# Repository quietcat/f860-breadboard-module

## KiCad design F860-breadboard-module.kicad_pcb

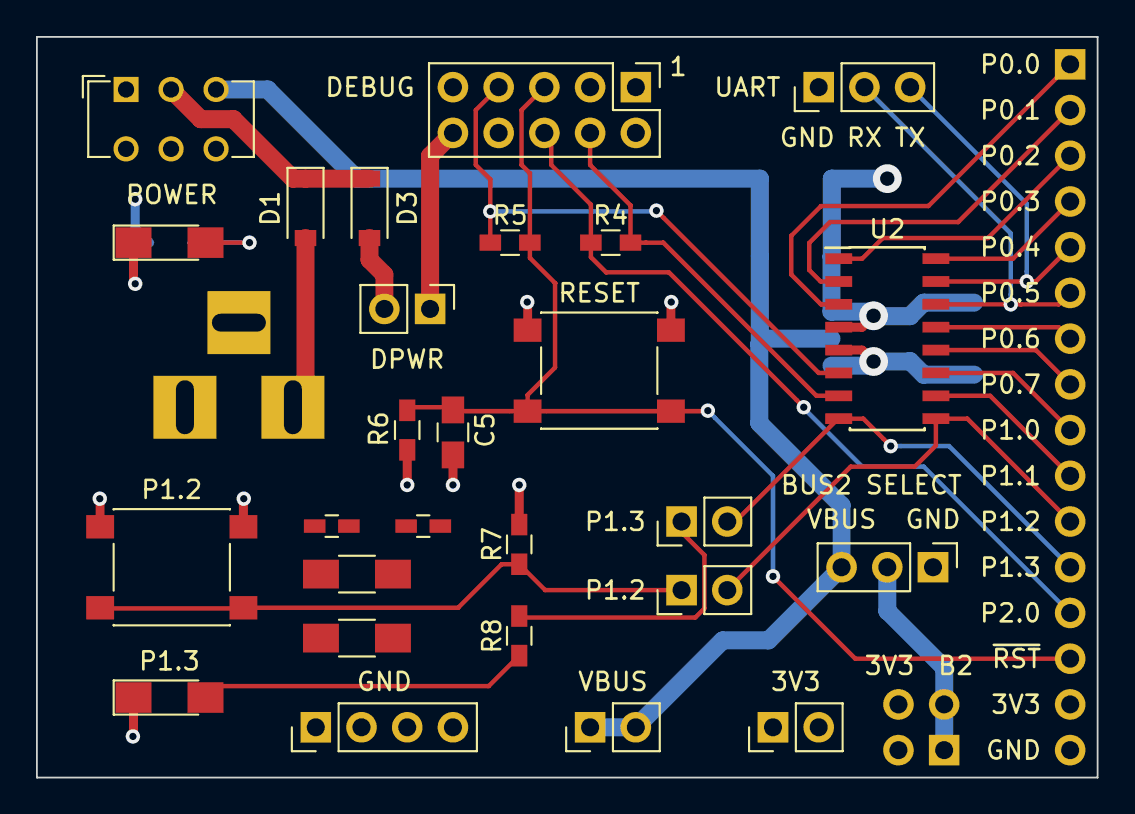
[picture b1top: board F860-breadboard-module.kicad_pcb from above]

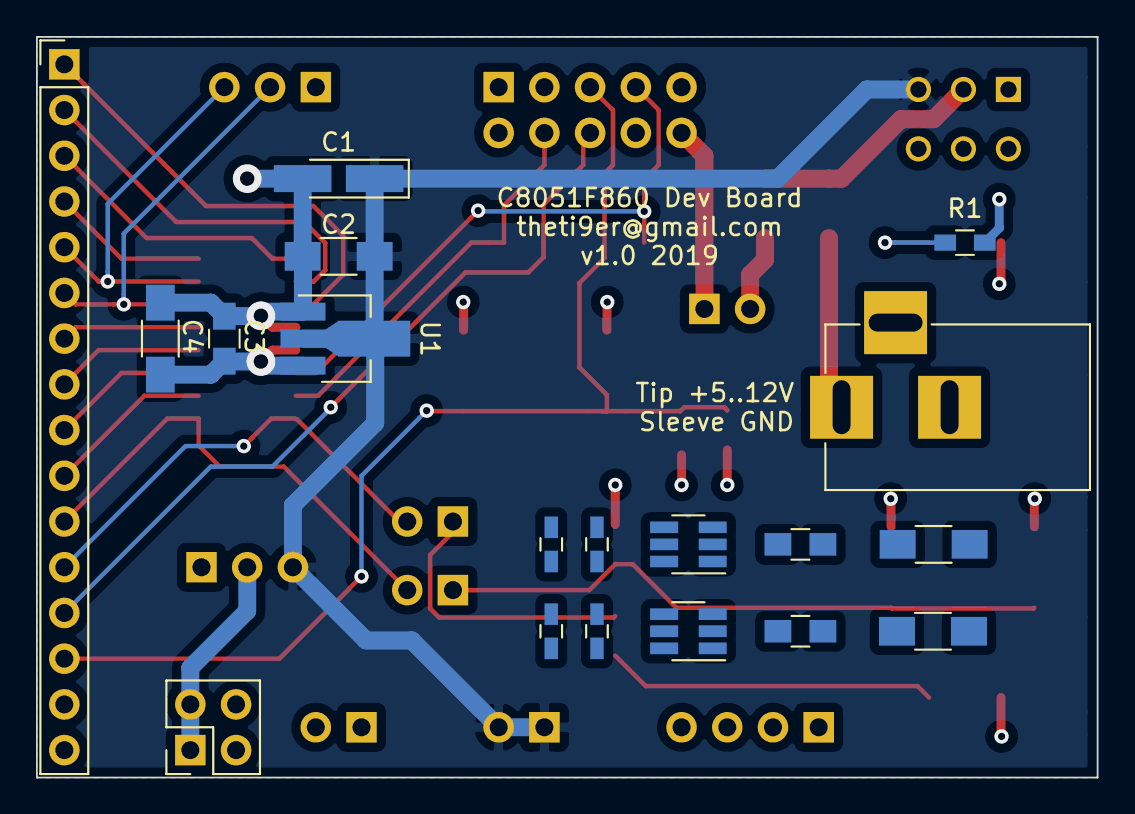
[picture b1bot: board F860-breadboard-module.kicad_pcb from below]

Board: 4 copper layers, 58.9 x 41.1 mm, 32 parts (9 on the bottom side), 28 nets.

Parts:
C1: 22.0; CP_Tantalum_Case-A_EIA-3216-18_Hand
C2, C4: 1.0; C_1206_HandSoldering
C3, C5: 0.1; C_0805_HandSoldering
D1, D3: STPS140Z; D_SOD-123
D2: PWR; LED_1206_HandSoldering
D4: P1.3; LED_1206_HandSoldering
J1: 5-12V; BARREL_JACK
J2: BOARD; Socket_Strip_Straight_1x16_Pitch2.54mm
J3: BUS2 SELECT; Pin_Header_Straight_1x03_Pitch2.54mm
J4: BUS1-2; Pin_Header_Straight_2x02_Pitch2.54mm
J6: VBUS; Pin_Header_Straight_1x02_Pitch2.54mm
J7: 3V3; Pin_Header_Straight_1x02_Pitch2.54mm
J8: GND; Pin_Header_Straight_1x04_Pitch2.54mm
J9: UART; Pin_Header_Straight_1x03_Pitch2.54mm
J10: DEBUG; Pin_Header_Straight_2x05_Pitch2.54mm
JP1: DPWR; Pin_Header_Straight_1x02_Pitch2.54mm
JP2: P1.2; Pin_Header_Straight_1x02_Pitch2.54mm
JP3: P1.3; Pin_Header_Straight_1x02_Pitch2.54mm
R1, R8: 470; R_0603_HandSoldering
R4, R5, R6: 1K0; R_0603_HandSoldering
R7: 3K3; R_0603_HandSoldering
SW1: POWER; SW_CuK_JS202011CQN_DPDT_Straight
SW2: RESET; SW_SPST_PTS645
SW3: P1.2; SW_SPST_PTS645
U1: MCP1700-3302E_SOT89; SOT-89-3_Handsoldering
U2: C8051F860-C-GS; SOIC-16_3.9x9.9mm_Pitch1.27mm

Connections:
+3V3: C3.1, C4.1, J2.15, J4.3, J4.4, J7.1, J7.2, R1.1, R6.2, R7.1, U1.3, U2.5
/C2CK: J10.7, R5.1, U2.6
/C2D: J10.4, R4.1, U2.7
/P0_0: J2.1, U2.3
/P0_1: J2.2, U2.2
/P0_2: J2.3, U2.1
/P0_3: J2.4, U2.16
/P0_4: J2.5, J9.3, U2.15
/P0_5: J2.6, J9.2, U2.14
/P0_6: J2.7, U2.13
/P0_7: J2.8, U2.12
/P1_0: J2.9, U2.11
/P1_1: J2.10, U2.10
/P1_2: J2.11, JP2.2, U2.9
/P1_3: J2.12, JP3.2, U2.8
/P2_0: J2.13, J10.6, R4.2
/VBUS0: D1.1, D3.1, SW1.2
/~RST: C5.1, J2.14, J10.5, R5.2, R6.1, SW2.2
GND: C1.2, C2.2, C3.2, C4.2, C5.2, D2.1, D4.1, J1.2, J2.16, J3.1, J8.1, J8.2, J8.3, J8.4, J9.1, J10.2, J10.3, J10.9, SW2.1, SW3.1, U1.1, U2.4
unnamed: D1.2, J1.1
unnamed: D2.2, R1.2
unnamed: D3.2, JP1.2
unnamed: D4.2, R8.2
unnamed: J3.2, J4.1, J4.2
unnamed: J10.10, JP1.1
unnamed: JP2.1, R7.2, SW3.2
unnamed: JP3.1, R8.1
VBUS: C1.1, C2.1, J3.3, J6.1, J6.2, SW1.3, U1.2

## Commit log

2019-07-07 Initial commit - V1.0
2023-09-28 Rename index.md to index.html
